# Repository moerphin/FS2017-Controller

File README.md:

# FS2017-Controller
This is a simple button box for FS2017, based on Arduino Leonardo with 17 joystick buttons. (Switch '0' turns the backlight.)<br>
Components:<br>
-Arduino sketch<br>
-PCB design (eagle)<br>
-BOM<br>
-Autocad design (dwg) for the top of the box<br>
<br>
# !!! Need to redesign! Missing pull-up resistors! !!!

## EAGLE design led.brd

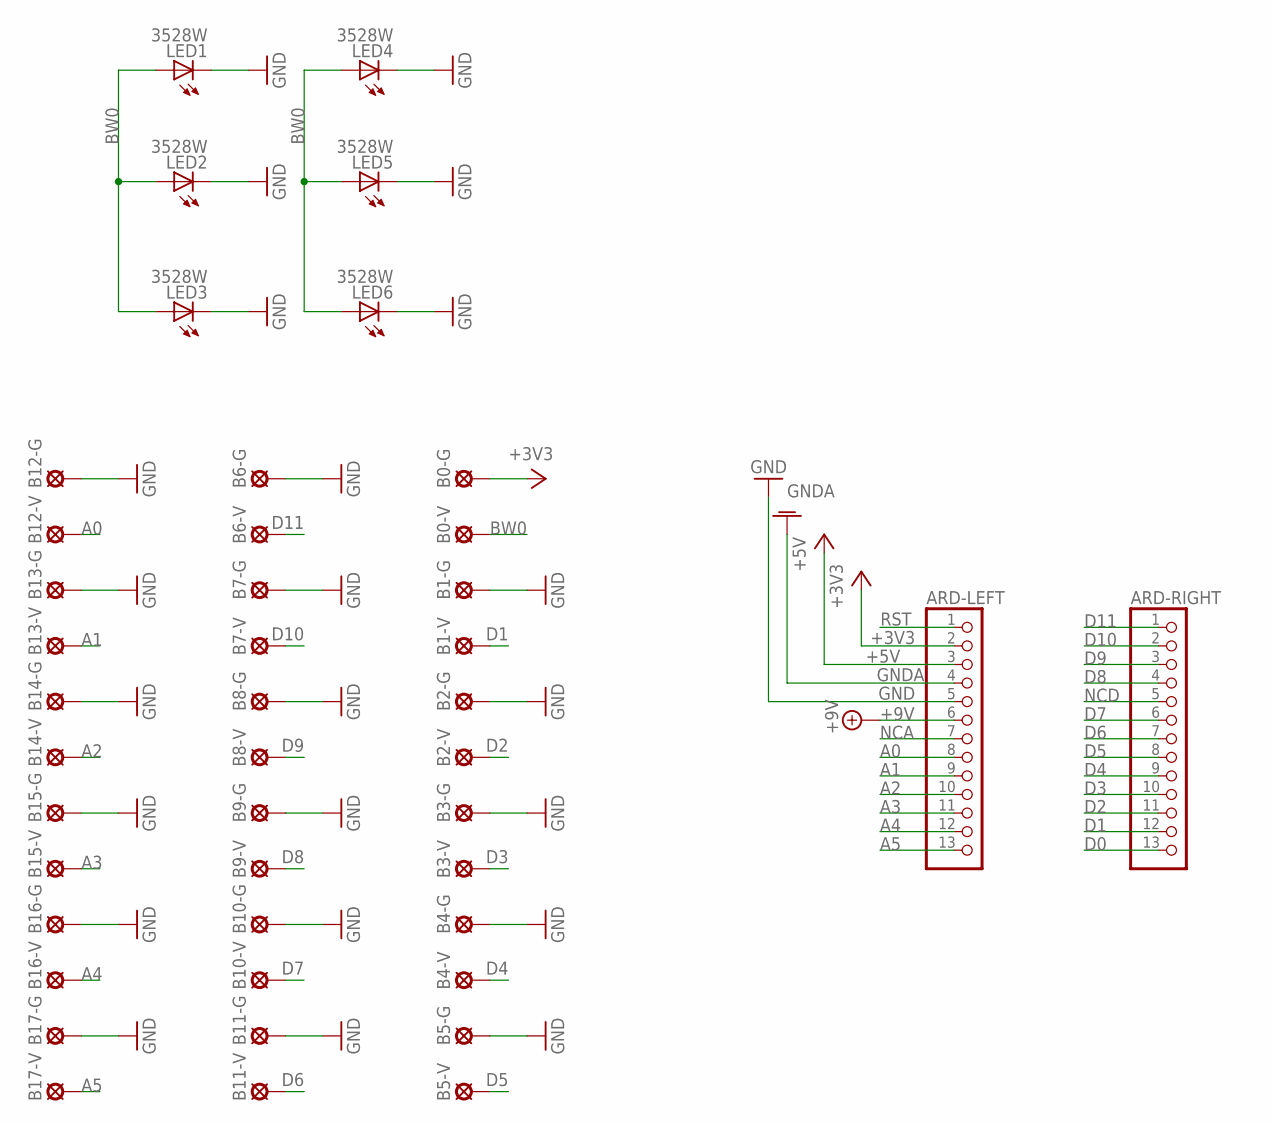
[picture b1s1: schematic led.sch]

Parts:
ARD-LEFT: PINHD-1X13; 1X13
ARD-RIGHT: PINHD-1X13; 1X13
B0-G, B0-V, B1-G, B1-V, B2-G, B2-V, B3-G, B3-V, B4-G, B4-V, B5-G, B5-V, B6-G, B6-V, B7-G, B7-V, B8-G, B8-V, B9-G, B9-V, B10-G, B10-V, B11-G, B11-V, B12-G, B12-V, B13-G, B13-V, B14-G, B14-V, B15-G, B15-V, B16-G, B16-V, B17-G, B17-V: LSP10
LED1, LED2, LED3, LED4, LED5, LED6: 3528W; P-LCC-2

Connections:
+3V3: ARD-LEFT.2, B0-G.MP
+5V: ARD-LEFT.3
+9V: ARD-LEFT.6
A0: ARD-LEFT.8, B12-V.MP
A1: ARD-LEFT.9, B13-V.MP
A2: ARD-LEFT.10, B14-V.MP
A3: ARD-LEFT.11, B15-V.MP
A4: ARD-LEFT.12, B16-V.MP
A5: ARD-LEFT.13, B17-V.MP
BW0: B0-V.MP, LED1.A, LED2.A, LED3.A, LED4.A, LED5.A, LED6.A
D0: ARD-RIGHT.13
D1: ARD-RIGHT.12, B1-V.MP
D2: ARD-RIGHT.11, B2-V.MP
D3: ARD-RIGHT.10, B3-V.MP
D4: ARD-RIGHT.9, B4-V.MP
D5: ARD-RIGHT.8, B5-V.MP
D6: ARD-RIGHT.7, B11-V.MP
D7: ARD-RIGHT.6, B10-V.MP
D8: ARD-RIGHT.4, B9-V.MP
D9: ARD-RIGHT.3, B8-V.MP
D10: ARD-RIGHT.2, B7-V.MP
D11: ARD-RIGHT.1, B6-V.MP
GND: ARD-LEFT.5, B1-G.MP, B2-G.MP, B3-G.MP, B4-G.MP, B5-G.MP, B6-G.MP, B7-G.MP, B8-G.MP, B9-G.MP, B10-G.MP, B11-G.MP, B12-G.MP, B13-G.MP, B14-G.MP, B15-G.MP, B16-G.MP, B17-G.MP, LED1.C, LED2.C, LED3.C, LED4.C, LED5.C, LED6.C
GNDA: ARD-LEFT.4
NCA: ARD-LEFT.7
NCD: ARD-RIGHT.5
RST: ARD-LEFT.1

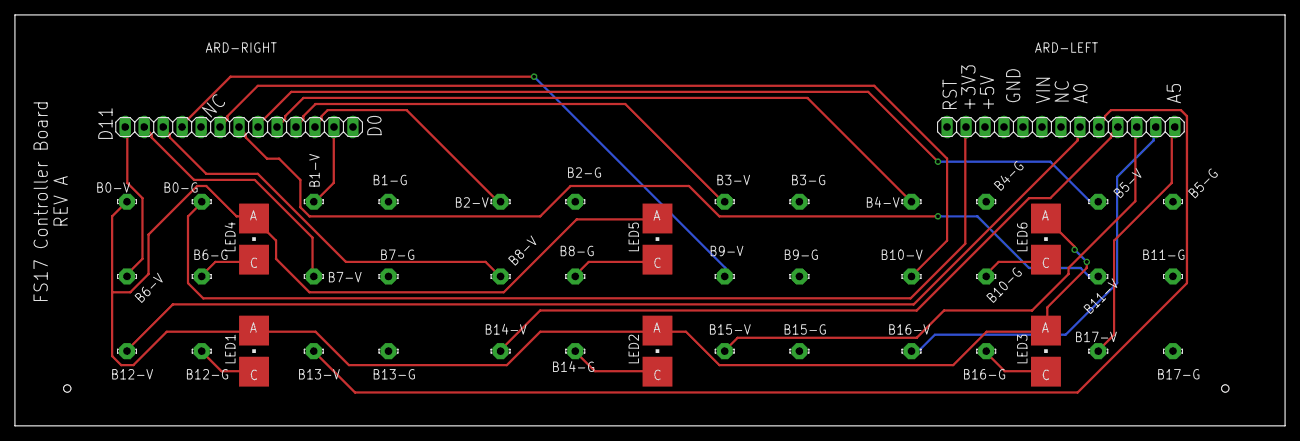
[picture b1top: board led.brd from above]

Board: 2 copper layers, 170.0 x 55.0 mm, 44 parts (0 on the bottom side), 20 nets.

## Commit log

2017-12-30 Rename led.sch to hardware/board.sch
2017-12-30 Rename led.brd to hardware/board.brd
2017-12-30 Vector graphic for the alu box top cutting
2017-12-30 Vector graphics for plexi cutting.
    Material:
    3mm opal plexi with red foil cover.
2017-12-30 Some pics
2017-12-30 Arduino sketch
2017-12-30 Joystick arduino library
